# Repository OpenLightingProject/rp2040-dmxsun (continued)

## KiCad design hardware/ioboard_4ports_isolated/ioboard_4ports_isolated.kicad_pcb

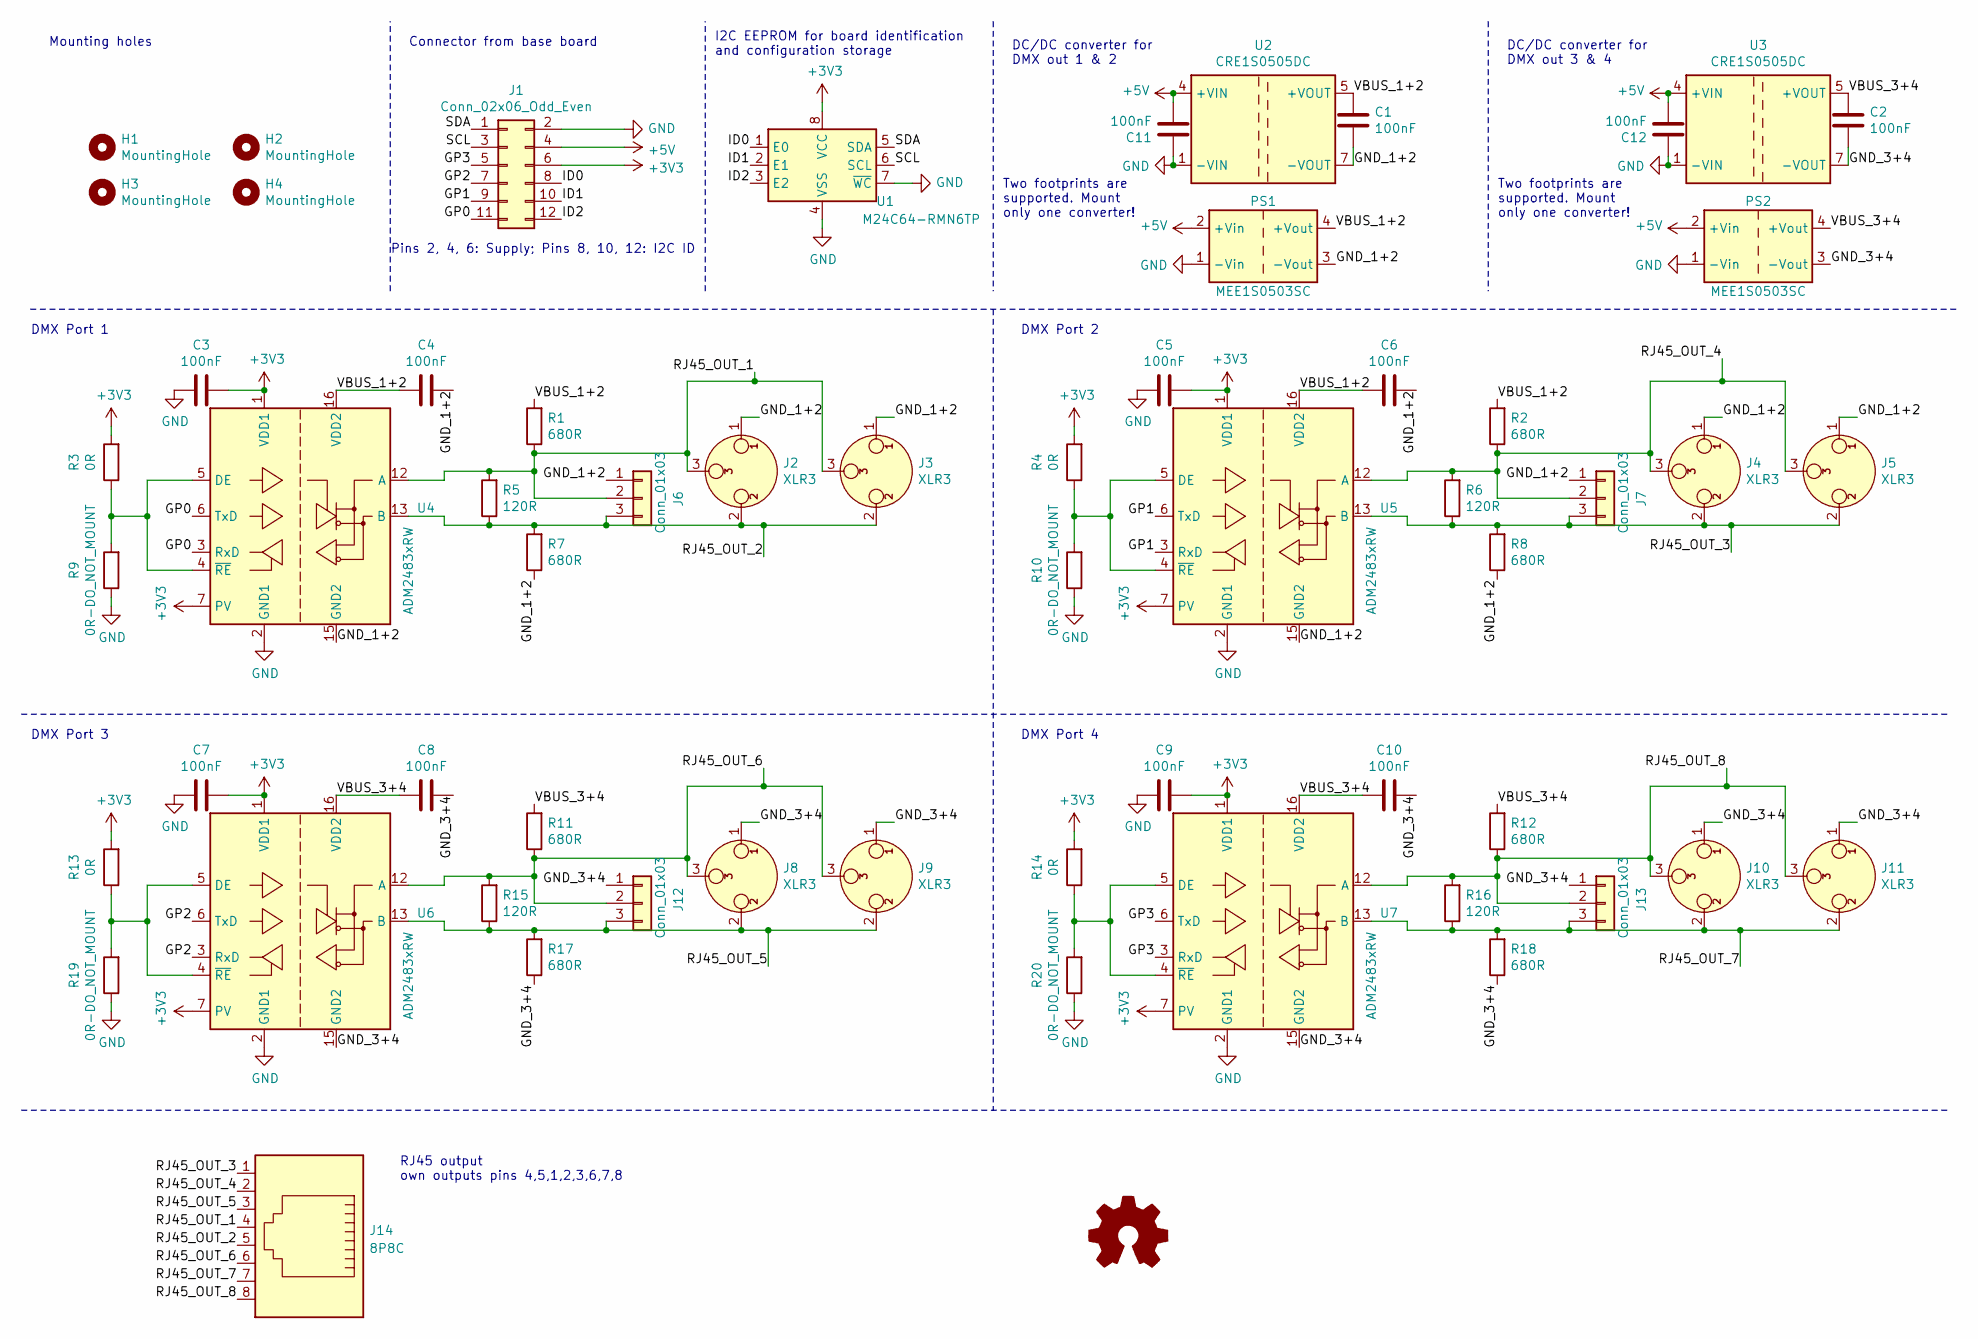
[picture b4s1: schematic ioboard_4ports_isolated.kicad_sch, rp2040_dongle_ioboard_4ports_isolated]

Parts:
C1, C2, C3, C4, C5, C6, C7, C8, C9, C10, C11, C12: 100nF; C_0603_1608Metric; LCSC C14663
H1, H2, H3, H4: MountingHole; MountingHole_3.2mm_M3
J1: Conn_02x06_Odd_Even; PinHeader_2x06_P2.54mm_Vertical
J2, J4, J8, J10: XLR3; Jack_XLR_Neutrik_NC3FAAH_Horizontal
J3, J5, J9, J11: XLR3; Jack_XLR_Neutrik_NC3FD-H_Horizontal
J6, J7, J12, J13: Conn_01x03; PinHeader_1x03_P2.54mm_Vertical
J14: 8P8C; RJ45_Sparkfun
PS1, PS2: MEE1S0503SC; Converter_DCDC_muRata_CRE1xxxxxx3C_THT
R1, R2, R7, R8, R11, R12, R17, R18: 680R; R_0603_1608Metric_Pad0.98x0.95mm_HandSolder; LCSC C23228
R3, R4, R13, R14: 0R; R_0805_2012Metric_Pad1.20x1.40mm_HandSolder; LCSC C17477
R5, R6, R15, R16: 120R; R_0603_1608Metric_Pad0.98x0.95mm_HandSolder; LCSC C22787
R9, R10, R19, R20: 0R-DO_NOT_MOUNT; R_0805_2012Metric_Pad1.20x1.40mm_HandSolder; LCSC C17477
SYM1: Logo_Open_Hardware_Small; OSHW-Logo2_7.3x6mm_SilkScreen
U1: M24C64-RMN6TP; SOIC-8_3.9x4.9mm_P1.27mm; LCSC C79988
U2, U3: CRE1S0505DC; Converter_DCDC_muRata_CRE1xxxxxxDC_THT
U4, U5, U6, U7: ADM2483xRW; SOIC-16W_7.5x10.3mm_P1.27mm; LCSC C9637

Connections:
+3V3: C3.1, C5.1, C7.1, C9.1, J1.6, R3.2, R4.2, R13.2, R14.2, U1.8 (VCC), U4.1 (VDD1), U4.7 (PV), U5.1 (VDD1), U5.7 (PV), U6.1 (VDD1), U6.7 (PV), U7.1 (VDD1), U7.7 (PV)
+5V: C11.1, C12.1, J1.4, PS1.2 (+Vin), PS2.2 (+Vin), U2.4 (+VIN), U3.4 (+VIN)
/GND_1+2: C1.1, C4.1, C6.1, J2.1, J3.1, J4.1, J5.1, J6.1, J7.1, PS1.3 (-Vout), R7.1, R8.1, U2.7 (-VOUT), U4.9 (GND2), U4.15 (GND2), U5.9 (GND2), U5.15 (GND2)
/GND_3+4: C2.1, C8.1, C10.1, J8.1, J9.1, J10.1, J11.1, J12.1, J13.1, PS2.3 (-Vout), R17.1, R18.1, U3.7 (-VOUT), U6.9 (GND2), U6.15 (GND2), U7.9 (GND2), U7.15 (GND2)
/GP0: J1.11, U4.3 (RxD), U4.6 (TxD)
/GP1: J1.9, U5.3 (RxD), U5.6 (TxD)
/GP2: J1.7, U6.3 (RxD), U6.6 (TxD)
/GP3: J1.5, U7.3 (RxD), U7.6 (TxD)
/ID0: J1.8, U1.1 (E0)
/ID1: J1.10, U1.2 (E1)
/ID2: J1.12, U1.3 (E2)
/RJ45_OUT_1: J2.3, J3.3, J6.2, J14.4, R1.1, R5.2, U4.12 (A)
/RJ45_OUT_2: J2.2, J3.2, J6.3, J14.5, R5.1, R7.2, U4.13 (B)
/RJ45_OUT_3: J4.2, J5.2, J7.3, J14.1, R6.1, R8.2, U5.13 (B)
/RJ45_OUT_4: J4.3, J5.3, J7.2, J14.2, R2.1, R6.2, U5.12 (A)
/RJ45_OUT_5: J8.2, J9.2, J12.3, J14.3, R15.1, R17.2, U6.13 (B)
/RJ45_OUT_6: J8.3, J9.3, J12.2, J14.6, R11.1, R15.2, U6.12 (A)
/RJ45_OUT_7: J10.2, J11.2, J13.3, J14.7, R16.1, R18.2, U7.13 (B)
/RJ45_OUT_8: J10.3, J11.3, J13.2, J14.8, R12.1, R16.2, U7.12 (A)
/SCL: J1.3, U1.6 (SCL)
/SDA: J1.1, U1.5 (SDA)
/VBUS_1+2: C1.2, C4.2, C6.2, PS1.4 (+Vout), R1.2, R2.2, U2.5 (+VOUT), U4.16 (VDD2), U5.16 (VDD2)
/VBUS_3+4: C2.2, C8.2, C10.2, PS2.4 (+Vout), R11.2, R12.2, U3.5 (+VOUT), U6.16 (VDD2), U7.16 (VDD2)
GND: C3.2, C5.2, C7.2, C9.2, C11.2, C12.2, J1.2, PS1.1 (-Vin), PS2.1 (-Vin), R9.1, R10.1, R19.1, R20.1, U1.4 (VSS), U1.7 (~WC), U2.1 (-VIN), U3.1 (-VIN), U4.2 (GND1), U4.8 (GND1), U5.2 (GND1), U5.8 (GND1), U6.2 (GND1), U6.8 (GND1), U7.2 (GND1), U7.8 (GND1)
unnamed: R3.1, R9.2, U4.4 (~RE), U4.5 (DE)
unnamed: R4.1, R10.2, U5.4 (~RE), U5.5 (DE)
unnamed: R13.1, R19.2, U6.4 (~RE), U6.5 (DE)
unnamed: R14.1, R20.2, U7.4 (~RE), U7.5 (DE)

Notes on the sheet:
DMX Port 1
DMX Port 2
DC/DC converter for DMX out 1 & 2
Mounting holes
DMX Port 3
DC/DC converter for DMX out 3 & 4
Pins 2, 4, 6: Supply; Pins 8, 10, 12: I2C ID
Two footprints are supported. Mount only one converter!
RJ45 output own outputs pins 4,5,1,2,3,6,7,8
Connector from base board
DMX Port 4
I2C EEPROM for board identification and configuration storage

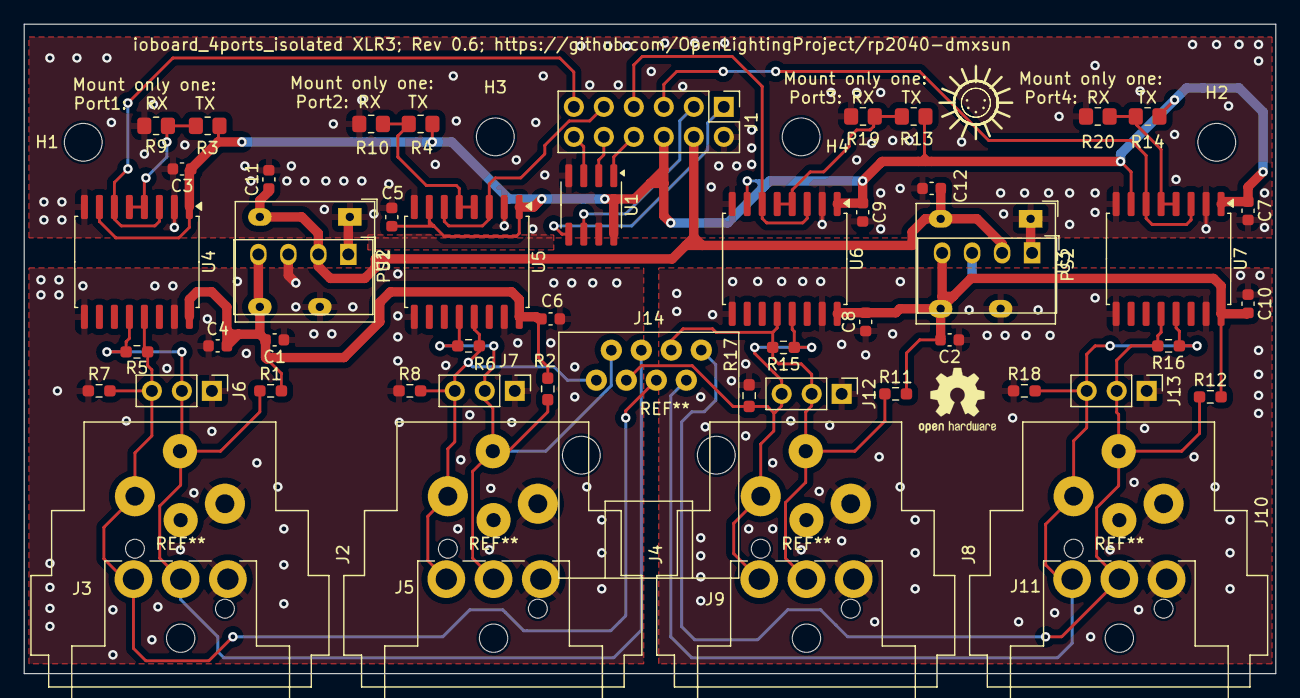
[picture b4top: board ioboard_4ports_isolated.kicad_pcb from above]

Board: 2 copper layers, 106.0 x 55.0 mm, 60 parts (0 on the bottom side), 28 nets.

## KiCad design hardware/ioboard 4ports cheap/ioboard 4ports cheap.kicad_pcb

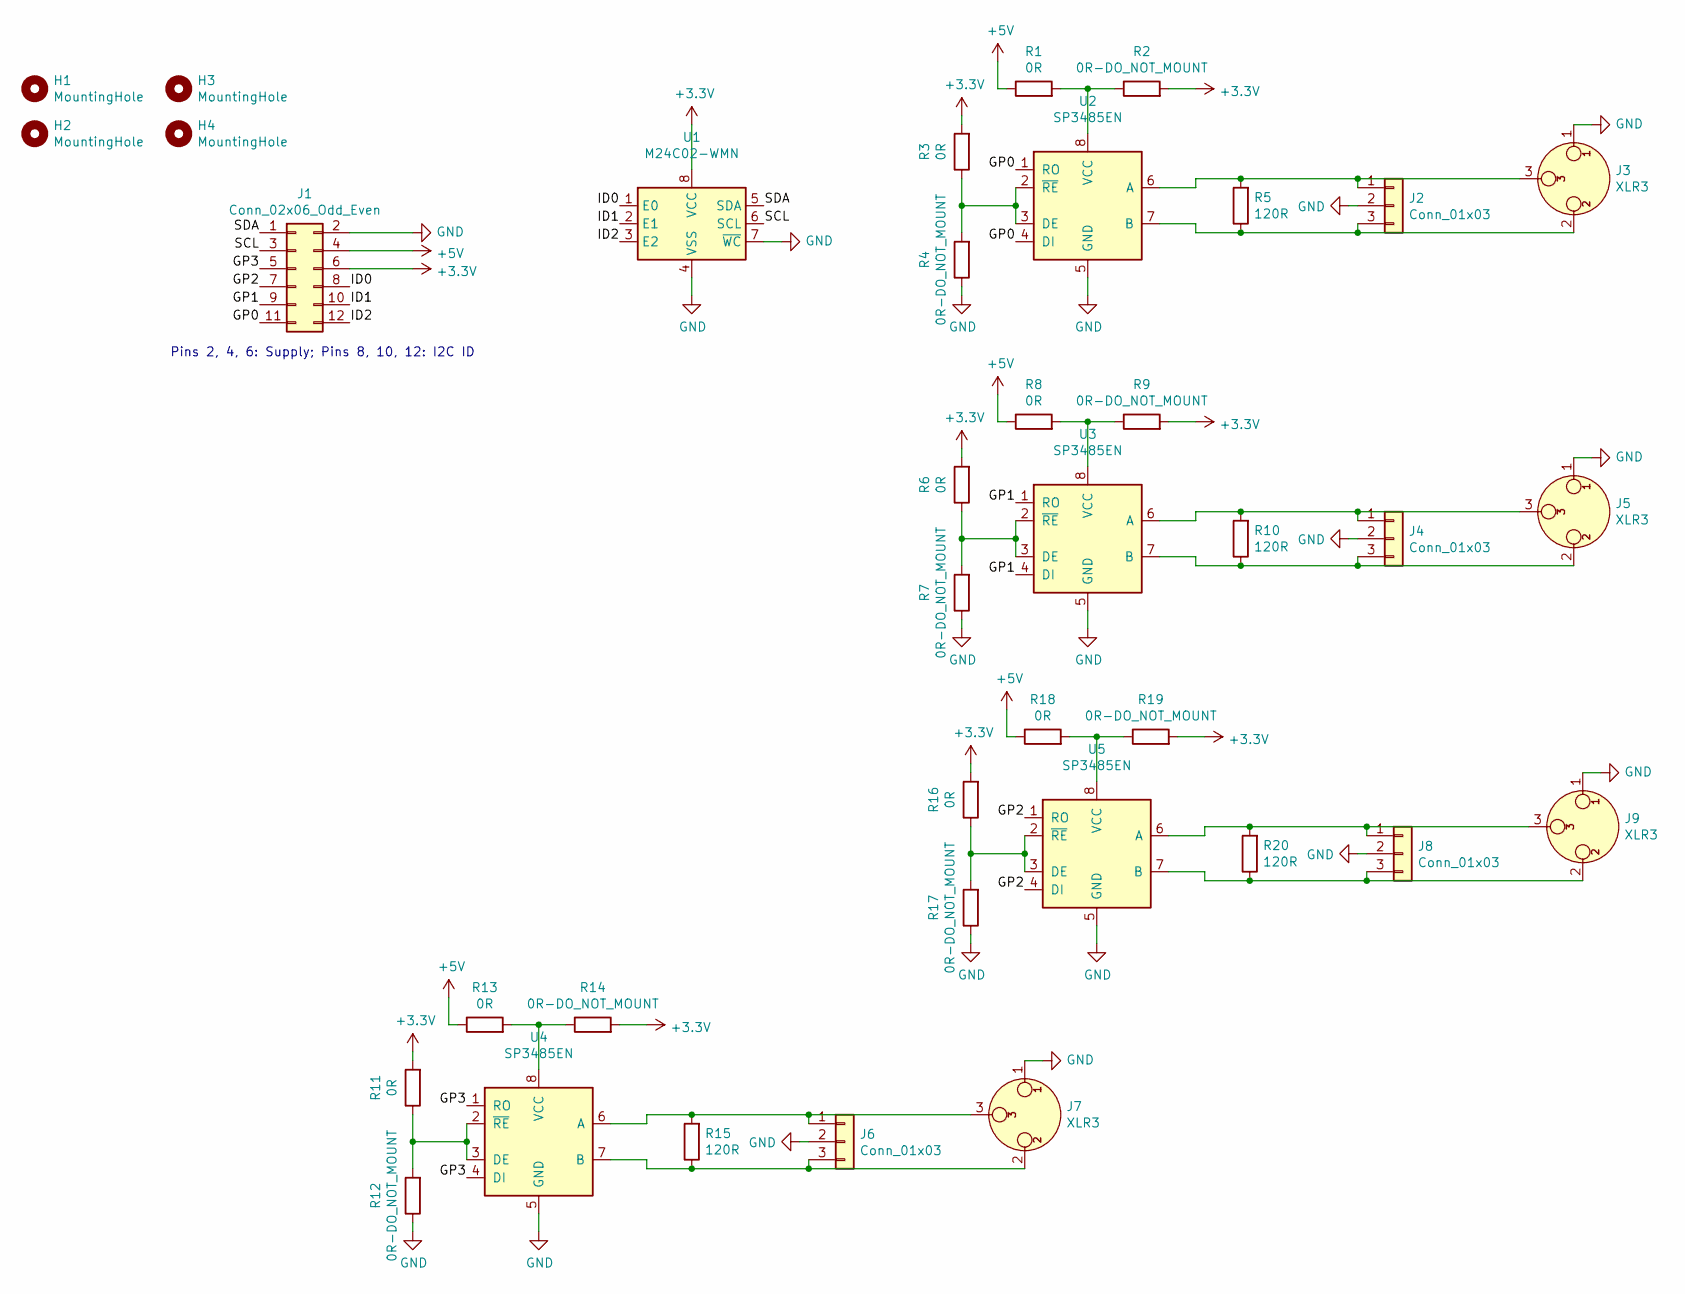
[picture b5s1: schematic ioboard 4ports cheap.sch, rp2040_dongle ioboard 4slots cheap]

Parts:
H1, H2, H3, H4: MountingHole; MountingHole_3.2mm_M3
J1: Conn_02x06_Odd_Even; PinHeader_2x06_P2.54mm_Vertical
J2, J4, J6, J8: Conn_01x03; PinHeader_1x03_P2.54mm_Vertical
J3, J5, J7, J9: XLR3; Jack_XLR_Neutrik_NC3FAAH_Horizontal
R1, R3, R6, R8, R11, R13, R16, R18: 0R; R_0603_1608Metric_Pad0.98x0.95mm_HandSolder
R2, R4, R7, R9, R12, R14, R17, R19: 0R-DO_NOT_MOUNT; R_0603_1608Metric_Pad0.98x0.95mm_HandSolder
R5, R10, R15, R20: 120R; R_0603_1608Metric_Pad0.98x0.95mm_HandSolder
U1: M24C02-WMN; SOIC-8_3.9x4.9mm_P1.27mm
U2, U3, U4, U5: SP3485EN; SOIC-8_3.9x4.9mm_P1.27mm

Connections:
+3V3: J1.6, R2.2, R3.2, R6.2, R9.2, R11.2, R14.2, R16.2, R19.2, U1.8 (VCC)
+5V: J1.4, R1.1, R8.1, R13.1, R18.1
/GP0: J1.11, U2.1 (RO), U2.4 (DI)
/GP1: J1.9, U3.1 (RO), U3.4 (DI)
/GP2: J1.7, U5.1 (RO), U5.4 (DI)
/GP3: J1.5, U4.1 (RO), U4.4 (DI)
/ID0: J1.8, U1.1 (E0)
/ID1: J1.10, U1.2 (E1)
/ID2: J1.12, U1.3 (E2)
/SCL: J1.3, U1.6 (SCL)
/SDA: J1.1, U1.5 (SDA)
GND: J1.2, J2.2, J3.1, J4.2, J5.1, J6.2, J7.1, J8.2, J9.1, R4.1, R7.1, R12.1, R17.1, U1.4 (VSS), U1.7 (~WC), U2.5 (GND), U3.5 (GND), U4.5 (GND), U5.5 (GND)
unnamed: J2.1, J3.3, R5.2, U2.6 (A)
unnamed: J2.3, J3.2, R5.1, U2.7 (B)
unnamed: J4.1, J5.3, R10.2, U3.6 (A)
unnamed: J4.3, J5.2, R10.1, U3.7 (B)
unnamed: J6.1, J7.3, R15.2, U4.6 (A)
unnamed: J6.3, J7.2, R15.1, U4.7 (B)
unnamed: J8.1, J9.3, R20.2, U5.6 (A)
unnamed: J8.3, J9.2, R20.1, U5.7 (B)
unnamed: R1.2, R2.1, U2.8 (VCC)
unnamed: R3.1, R4.2, U2.2 (~RE~), U2.3 (DE)
unnamed: R6.1, R7.2, U3.2 (~RE~), U3.3 (DE)
unnamed: R8.2, R9.1, U3.8 (VCC)
unnamed: R11.1, R12.2, U4.2 (~RE~), U4.3 (DE)
unnamed: R13.2, R14.1, U4.8 (VCC)
unnamed: R16.1, R17.2, U5.2 (~RE~), U5.3 (DE)
unnamed: R18.2, R19.1, U5.8 (VCC)

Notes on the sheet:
Pins 2, 4, 6: Supply; Pins 8, 10, 12: I2C ID

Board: 2 copper layers, 38 parts (0 on the bottom side), 28 nets, no tracks yet.

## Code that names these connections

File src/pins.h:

// GPIO pins used by the rp2040-dmxsun
// GPIO numbers of the RP2040 chip,
// NOT hardware pin numbers of the pico module!
// All in one file for easy reference

#include <bsp/board.h>          // On-board-LED

// I2C to IO boards for detection and configuration
// (Every IO board has one 2048kbit EEPROM)
#define PIN_I2C_SCL     0
#define PIN_I2C_SDA     1

// SPI to the optional nRF24L01+ module
#define PIN_SPI_CLK     2
#define PIN_SPI_MOSI    3
#define PIN_SPI_MISO    4
#define PIN_SPI_CS0     5
#define PIN_RF24_CE    28

// IO board 00
#define PIN_IO00_0      6
#define PIN_IO00_1      7
#define PIN_IO00_2      8
#define PIN_IO00_3      9

// IO board 01
#define PIN_IO01_0     10
#define PIN_IO01_1     11
#define PIN_IO01_2     12
#define PIN_IO01_3     13

// IO board 10
#define PIN_IO10_0     14
#define PIN_IO10_1     15
#define PIN_IO10_2     16
#define PIN_IO10_3     17

// IO board 11
#define PIN_IO11_0     18
#define PIN_IO11_1     19
#define PIN_IO11_2     20
#define PIN_IO11_3     21

// Pico's on-board, single-color status LED
// If a regular "Pico" is detected at runtime => Port 25
// If a Pico-W is detected at runtime => GPIO 0 of the cyw43
#define PIN_LED_PICO   25
#define PIN_LED_PICOW  CYW43_WL_GPIO_LED_PIN

// WS2812-based status LEDs
#define PIN_LEDS       22

// Helper pin for DMX TX (DriverEnable output)
// this is mainly useful to trigger an oscilloscope to check the
// generated DMX frames
#define PIN_TRIGGER    26

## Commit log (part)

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2021-05-18 Fix regen-fsdata to work in GitHub Actions, again (Zopfli headers are in subdir on Ubuntu)
2021-05-19 Fail faster if no rf24-module is connected
2021-05-19 Allow fetching all 24 DMX buffers via HTTP
2021-06-13 Use snappy compression for wireless spectrum as well. Mostly to prove it's actually working and decompressable in the browser. It is :)
2021-06-20 Add jsoncpp library
2021-07-05 WiP: Refine boardConfig with bit fields, start implementing localDmx and rudimentary patch handling
2021-07-06 Make local DMX TX work. Not correct content yet ;)
2021-07-06 Add some easy sanitizing on log messages
2021-07-09 Move all static www files from www (which will be auto-generated) to wwwsrc/public (from where it is copied to www). Also fix a build error in log.cpp
2021-07-09 Log less and add a line counter to the log output so a consumer can properly merge log buffers
2021-07-09 Add number of entries remaining in the buffer to the log fetched via web server
2021-07-10 Implement a very basic console (displaying and setting single channels via sliders)
2021-07-11 Web App: Introduce a global urlPrefix so we don't have to set the prefix for every URL
2021-07-14 Implement wireless data transmission. Very crude yet but working :D
2021-07-26 Implement TX part of the new broadcast protocol, using data compression and chunking
2021-07-28 Temporarily remove log sanitizing since it seems to cause memory issues
2021-07-31 Wireless DMX: Change the protocol a bit and finish implementing compressed and raw DMX frames
2021-08-01 Some more wireless tuning
2021-08-04 Rename ECM -> NCM, drop RNDIS and fix the MS OS 2.0 descriptor so that the NCM from code https://github.com/hathach/tinyusb/pull/550 works out-of-the-box on Linux, macOS and Windows
2021-08-06 DHCP server: don't send DNS info, wireless RX: Add some sanity checking. And some comment updates
2021-08-09 Initial Artnet-In implementation
2021-09-29 Cleanups and comments
2021-09-29 Protect the logBuffer even more so the dongle doesn't crash when the log buffer is requested via web
2021-09-30 Version 0.3.0
2021-10-06 Simplify stdio_usb.c so it doesn't have it's own interrupt-based loop calling tud_task since we call it in our main loop anyways
2021-10-06 Wireless: More strict input sanitization to avoid crash by integer underflow and following out-of-bounds writing
2021-10-08 Honestly too much for one commit but here we go: - StatusLeds: New methods to turn on and single colors and add blinking mechanism. Adapt all users - StatusLeds: Add new cyclicTask method to implemen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
2021-10-08 WebUI: Fetch overview until it succeeds
2021-10-10 Reduce logging in ArtNet- and E1.31 receiver code and move all LED tasks from core0 to core1 to make 16 universes IN work reliably
2021-10-10 Fix Not-a-typo to make codespell happy
2021-10-11 Version 0.8.1
2021-10-12 Revert App.js that should not have been comitted
2021-10-12 Prepare old wireless code for the protocol changes introduced by EDP (command changes, universeId moves from chunk header to packetHeader) so we can test old RX code with new TX code and vice verssa.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
2021-10-12 Version 0.8.2
2021-10-13 Implement incoming packet handling in EDP and use it in the wireless code
2021-10-14 Fix codespell typo
2021-10-15 Assign ourselves the 1209/2040 USB IDs, assuming we will request it officially.
2021-10-18 Re-enable CRC check since it's working now
2021-10-18 Remove no longer needed protocol data types in wireless.h since it has all been moved to edp
2021-10-27 lwIP: Add callbacks for network interface link and status changes. Might be later used to control the USB status LED
2021-10-27 Convert some more enums to enumFactory-using definitions
2021-10-27 Make the port params in the board-specific section of the config an array so we can loop over it
2021-11-01 Implement writing the config to one of the IO boards
2021-11-02 Add editable and optimized versions of XLR plugs and sockets
2021-11-08 WebServer: Use std::map<std::string, std::string> for incoming parameters. And add functions to enable and disable specific configurations
2021-11-08 Fix typo
2021-11-09 Fix a react warning
2021-11-16 WebUI: Properly initialize BoardStatus' tooltips and fix class name of StatusLeds
2021-11-16 WebUI: Also make it possible to change the board's IP (includes chaning the host IP as well)
2021-11-20 Use the official pico-sdk 1.3.0 in the GitHub Action
2021-11-21 WebUI: Fix some react runtime-errors and start the Wireless page
2021-11-24 WiP: Wireless config API
2021-11-26 Prepare Wireless page for more information that just the spectrum
2021-11-26 PartyMode, part 1: Functionality
2021-12-22 Update wwwsrc/src/Home.js
    Fixed a typo found by @peternewman
2021-12-22 Add non-finished 4ports isolated IO board
2021-12-22 Baseboard: Add some capacitors between GND and supply lines (nRF24 connector, RPi Pico, status LEDs and IO connectors)
2021-12-22 Refine placement of one capacitor
2021-12-22 More error ignoring rules
2021-12-22 Add ioboard_2ports_rdm_unisolated schematic and board
2021-12-22 Fix IO connector labelling
2021-12-22 Add ioboard 2ports rdm
2021-12-22 Re-work ioboard 4ports cheap. Should be production-ready
2021-12-22 Kicad action: one job for each board + trigger also when the workflow itself is changed
2021-12-22 Unify board naming and bump all to rev 0.2
2022-01-08 Big README update
2022-01-08 Additional README fixes
2022-01-09 Bump react-router-dom from 5.3.0 to 6.2.1 in /wwwsrc
    Bumps [react-router-dom](https://github.com/remix-run/react-router/tree/HEAD/packages/react-router-dom) from 5.3.0 to 6.2.1.
    - [Release notes](https://github.com/remix-run/react-router/releases)
    - [Commits](https://github.com/remix-run/react-router/commits/v6.2.1/packages/react-router-dom)
    ---
    updated-dependencies:
    - dependency-name: react-router-dom
2022-01-09 Adapt to new react-chartjs in Wireless page on Web UI
2022-01-11 Update README.md
    Convert some URLs to proper links
2022-03-02 Bump nerdyscout/kicad-exports from 2.2 to 2.3.1
    Bumps [nerdyscout/kicad-exports](https://github.com/nerdyscout/kicad-exports) from 2.2 to 2.3.1.
    - [Release notes](https://github.com/nerdyscout/kicad-exports/releases)
    - [Changelog](https://github.com/nerdyscout/kicad-exports/blob/main/CHANGELOG.md)
    - [Commits](https://github.com/nerdyscout/kicad-exports/compare/v2.2...v2.3.1)
    ---
    updated-dependencies:
2022-06-25 Minor updates of WebUI's dependencies
2022-06-25 Add some more version info (Pico-SDK, compiler) to the OverviewGet-Function of the web server
2022-10-26 Add planned, incompatible hardware change in the future
2022-11-07 Hardware: Remove two more unneeded files
2022-11-09 Fix gitignore Move NC3FD-H.pretty footprint library to a common location and update references Rework ioboard_2ports_rdm_isolated
2022-11-13 Add I2C expansion connectors and a Grove connector for the status LEDs
2022-11-14 Hardware: move some capacitors around to fix the DRC errors
2022-11-14 Fix typos in kibot config files (codespell)
2022-11-14 Baseboard: Add W5500 Mini (WIZ850io) module. Needs verification
2022-11-15 Convert the kibot workflow to a matrix job so we can export all boards
2022-11-15 Re-ignore ERC errors. Don't know why this wasn't commited the last time ...
2022-11-16 Bump nerdyscout/kicad-exports from 2.2 to 2.3
    Bumps [nerdyscout/kicad-exports](https://github.com/nerdyscout/kicad-exports) from 2.2 to 2.3.
    - [Release notes](https://github.com/nerdyscout/kicad-exports/releases)
    - [Changelog](https://github.com/nerdyscout/kicad-exports/blob/main/CHANGELOG.md)
    - [Commits](https://github.com/nerdyscout/kicad-exports/compare/v2.2...v2.3)
    ---
    updated-dependencies:
2022-11-27 Add the 2-slots-baseboard to the github action
2022-11-28 Add a IRQ config jumper for the nRF24 and the Wiz modules
2022-11-29 Replace Amphenol's RJ45 by the one by Sparkfun/4UCON
2022-11-30 Bump all boards to rev 0.6
2022-12-01 Try exporting more JLCPCB-ready files
2022-12-01 Choose a better name for the JLCPCB archive and include the correct files
2022-12-24 Re-work CMake files so that the Web UI is build properly and no longer hacky
2022-12-24 Fix indentation
2022-12-24 Revert "Fix a jsoncpp typo"
    This reverts commit 11916fbbcf848c8db09a5c3be8436c18340efb12.
2023-01-22 Update to the latest lwIP master + fixed DHCP client by sending a unique client id
2023-01-22 Bump WebUI dependencies
2023-01-23 Bump chart.js from 3.9.1 to 4.2.0 in /wwwsrc
    Bumps [chart.js](https://github.com/chartjs/Chart.js) from 3.9.1 to 4.2.0.
    - [Release notes](https://github.com/chartjs/Chart.js/releases)
    - [Commits](https://github.com/chartjs/Chart.js/compare/v3.9.1...v4.2.0)
    ---
    updated-dependencies:
    - dependency-name: chart.js
2023-01-29 wwwsrc dependencies update
2023-01-30 Fix reading the config from flash
2023-01-31 First steps for supporting the Pico-W
2023-02-01 Add doxygen to action builder so the cmake step doesn't break
2023-02-01 Try a matrix build for the pico and the pico_w
2023-02-04 Rename interfaces to one letter only
2023-02-04 Partly undo fd5e4781fa7f5282c24292471b047b15969b4d7e since renaming cyw43's lwIP interface breaks it .....
2023-02-04 Fix log content
2023-02-04 Last round of optimisations in WebUI + explanatory comment in boardconfig.h
2023-02-08 Codespell typo fix
2023-02-11 Support pico-sdk 1.5.0
2023-02-11 Add u8g2 library to talk to OLEDs
2023-03-05 Fix a compiler error that just appeared over night?
2023-03-28 Bump cssnano from 5.1.15 to 6.0.0 in /wwwsrc
    Bumps [cssnano](https://github.com/cssnano/cssnano) from 5.1.15 to 6.0.0.
    - [Release notes](https://github.com/cssnano/cssnano/releases)
    - [Commits](https://github.com/cssnano/cssnano/compare/cssnano@5.1.15...cssnano@6.0.0)
    ---
    updated-dependencies:
    - dependency-name: cssnano
2023-08-27 Further update WebApp dependencies
2024-01-04 Typo: use loadConfig.bind() in Load configuration button
2024-04-01 Bump @fullhuman/postcss-purgecss from 5.0.0 to 6.0.0 in /wwwsrc
    Bumps [@fullhuman/postcss-purgecss](https://github.com/FullHuman/purgecss) from 5.0.0 to 6.0.0.
    - [Release notes](https://github.com/FullHuman/purgecss/releases)
    - [Changelog](https://github.com/FullHuman/purgecss/blob/main/CHANGELOG.md)
    - [Commits](https://github.com/FullHuman/purgecss/compare/v5.0.0...v6.0.0)
    ---
    updated-dependencies:
2024-04-25 Bump cssnano from 6.1.2 to 7.0.0 in /wwwsrc
    Bumps [cssnano](https://github.com/cssnano/cssnano) from 6.1.2 to 7.0.0.
    - [Release notes](https://github.com/cssnano/cssnano/releases)
    - [Commits](https://github.com/cssnano/cssnano/compare/cssnano@6.1.2...cssnano@7.0.0)
    ---
    updated-dependencies:
    - dependency-name: cssnano
2024-06-06 Bump cssnano from 6.1.2 to 7.0.2 in /wwwsrc
    Bumps [cssnano](https://github.com/cssnano/cssnano) from 6.1.2 to 7.0.2.
    - [Release notes](https://github.com/cssnano/cssnano/releases)
    - [Commits](https://github.com/cssnano/cssnano/compare/cssnano@6.1.2...cssnano@7.0.2)
    ---
    updated-dependencies:
    - dependency-name: cssnano
2024-06-20 Bump cssnano-preset-advanced from 6.1.2 to 7.0.3 in /wwwsrc
    Bumps [cssnano-preset-advanced](https://github.com/cssnano/cssnano) from 6.1.2 to 7.0.3.
    - [Release notes](https://github.com/cssnano/cssnano/releases)
    - [Commits](https://github.com/cssnano/cssnano/compare/cssnano-preset-advanced@6.1.2...cssnano-preset-advanced@7.0.3)
    ---
    updated-dependencies:
    - dependency-name: cssnano-preset-advanced
2024-11-03 Update baseboards to KiCad 8, add copper keepout underneath Picos, add OpenHardware logo
2024-11-03 Same typo fixes in another file
2024-11-03 Fix/Exclude ERC and DRC errors on ioboards
2024-11-03 Update all footprints and ignore all other DRC warning on ioboards
2024-11-22 Bump purgecss from 6.0.0 to 7.0.2 in /wwwsrc
    Bumps [purgecss](https://github.com/FullHuman/purgecss) from 6.0.0 to 7.0.2.
    - [Release notes](https://github.com/FullHuman/purgecss/releases)
    - [Changelog](https://github.com/FullHuman/purgecss/blob/main/CHANGELOG.md)
    - [Commits](https://github.com/FullHuman/purgecss/compare/v6.0.0...v7.0.2)
    ---
    updated-dependencies:
2024-11-28 Make sure the Ubuntu 24.04 runners are used since they contain Node 20
